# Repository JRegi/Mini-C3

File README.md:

# MiniC3 - PCB

## Description:
MiniC3 is a PCB meant for amateur MiniSumo, featuring:
  -  ESP32-C3 Super Mini 
  -  MP2703 (Mini 360) Step-down module
  -  [Dual TB67H450FNG Driver module](https://github.com/JRegi/Driver-Module-TB67) (or [TA6586 Module](https://github.com/JRegi/Driver-Module-TA6586))

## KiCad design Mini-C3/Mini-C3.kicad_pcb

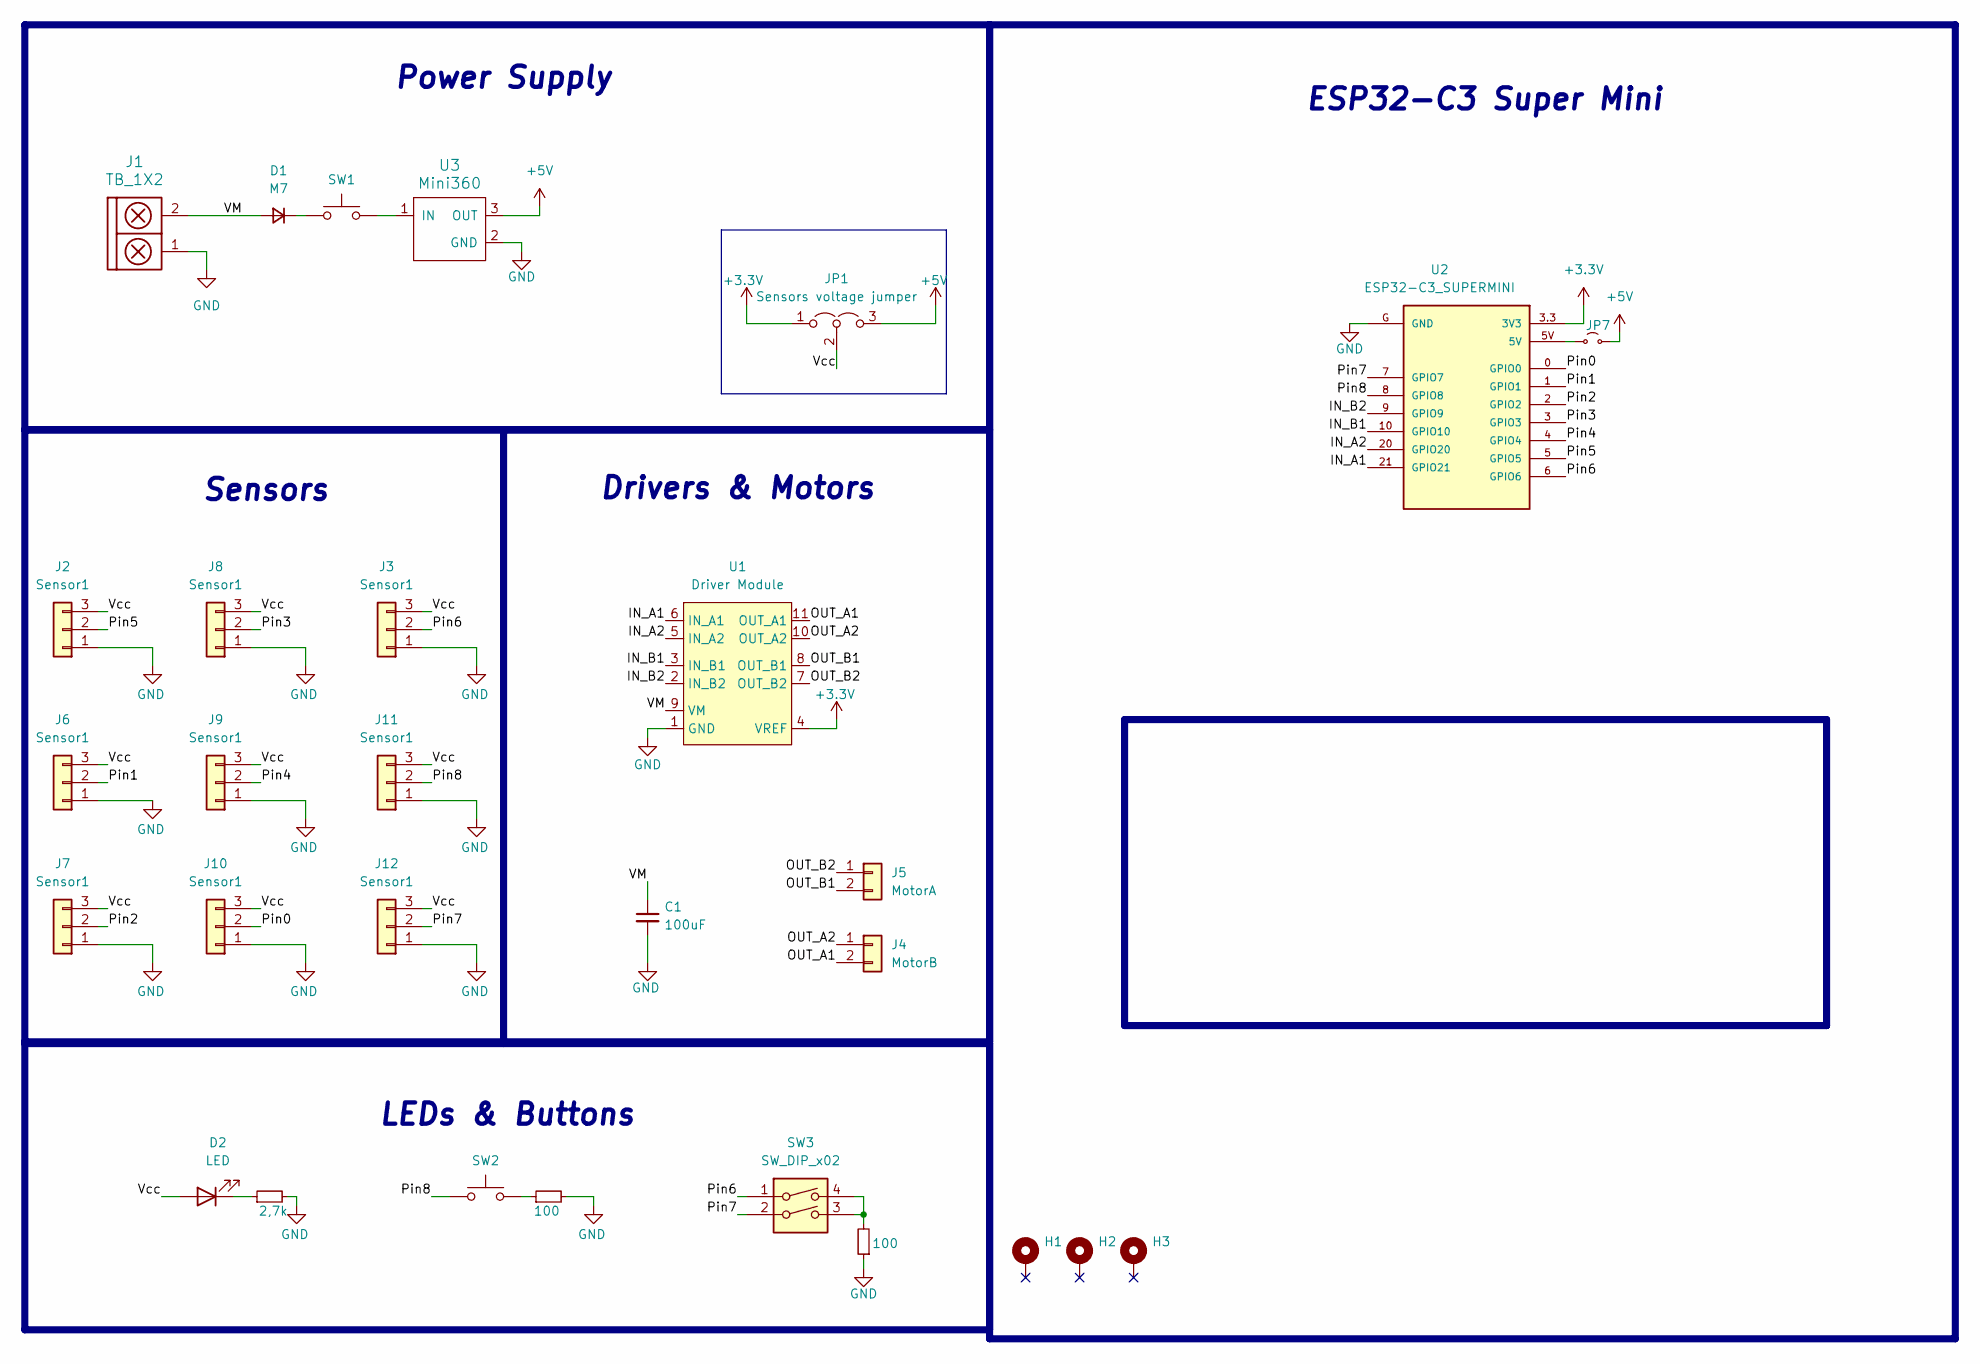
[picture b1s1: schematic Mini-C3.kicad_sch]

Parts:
C1: 100uF; C_Disc_D4.3mm_W1.9mm_P5.00mm
D1: M7; D_SMA
D2: LED; LED_0805_2012Metric
H1, H2, H3: MountingHole_Pad; MountingHole_2.2mm_M2_DIN965_Pad
J1: TB_1X2; MyPinHeader-01x02-vertical
J2, J3, J6, J7, J8, J9, J10, J11, J12: Sensor1; PinHeader_1x03_P2.54-THT
J4: MotorB; MyPinHeader-01x02
J5: MotorA; MyPinHeader-01x02
JP1: Sensors voltage jumper; SolderJumper-3_P2.0mm_Open_TrianglePad1.0x1.5mm
JP7: Jumper_2_Small_Open; SolderJumper-2_P1.3mm_Open_RoundedPad1.0x1.5mm
R1, R2: 100; R_0805_2012Metric
R13: 2,7k; R_0805_2012Metric
SW1: SW_Push; SW_Slide-03_P2.54_L9_W4_H7
SW2: SW_Push; SW_Tactile_SPST_NO_Straight_CK_PTS636Sx25SMTRLFS
SW3: SW_DIP_x02; SW_DIP_SPSTx02_Slide_6.7x6.64mm_W8.61mm_P2.54mm_LowProfile
U1: Driver Module; Dual-Driver-Module
U2: ESP32-C3_SUPERMINI; MODULE_ESP32-C3_SUPERMINI
U3: Mini360; Mini360_step-down

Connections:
+3.3V: JP1.1 (A), U1.4 (VREF), U2.3.3 (3V3)
+5V: JP1.3 (B), JP7.2 (B), U3.3 (OUT)
/IN_A1: U1.6 (IN_A1), U2.21 (GPIO21)
/IN_A2: U1.5 (IN_A2), U2.20 (GPIO20)
/IN_B1: U1.3 (IN_B1), U2.10 (GPIO10)
/IN_B2: U1.2 (IN_B2), U2.9 (GPIO9)
/OUT_A1: J4.2, U1.11 (OUT_A1)
/OUT_A2: J4.1, U1.10 (OUT_A2)
/OUT_B1: J5.2, U1.8 (OUT_B1)
/OUT_B2: J5.1, U1.7 (OUT_B2)
/Pin0: J10.2, U2.0 (GPIO0)
/Pin1: J6.2, U2.1 (GPIO1)
/Pin2: J7.2, U2.2 (GPIO2)
/Pin3: J8.2, U2.3 (GPIO3)
/Pin4: J9.2, U2.4 (GPIO4)
/Pin5: J2.2, U2.5 (GPIO5)
/Pin6: J3.2, SW3.1, U2.6 (GPIO6)
/Pin7: J12.2, SW3.2, U2.7 (GPIO7)
/Pin8: J11.2, SW2.1, U2.8 (GPIO8)
/VM: C1.1, D1.2 (A), J1.2, U1.9 (VM)
/Vcc: D2.2 (A), J2.3, J3.3, J6.3, J7.3, J8.3, J9.3, J10.3, J11.3, J12.3, JP1.2 (C)
GND: C1.2, J1.1, J2.1, J3.1, J6.1, J7.1, J8.1, J9.1, J10.1, J11.1, J12.1, R1.2, R2.1, R13.2, U1.1 (GND), U2.G (GND), U3.2 (GND)
unnamed: D1.1 (K), SW1.2
unnamed: D2.1 (K), R13.1
unnamed: JP7.1 (A), U2.5V
unnamed: R1.1, SW2.2
unnamed: R2.2, SW3.3, SW3.4
unnamed: SW1.1, U3.1 (IN)

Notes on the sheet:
Sensors
Power Supply
LEDs & Buttons
ESP32-C3 Super Mini
Drivers & Motors

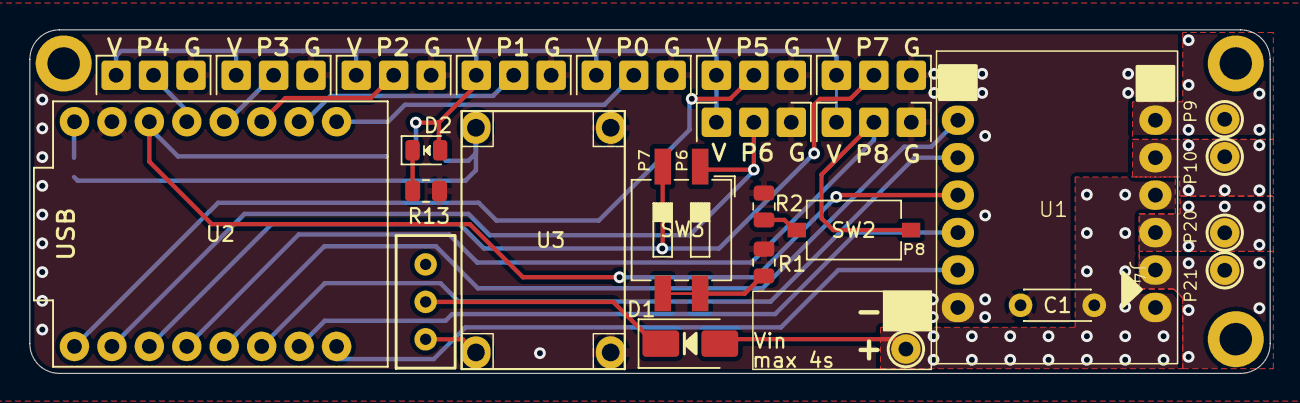
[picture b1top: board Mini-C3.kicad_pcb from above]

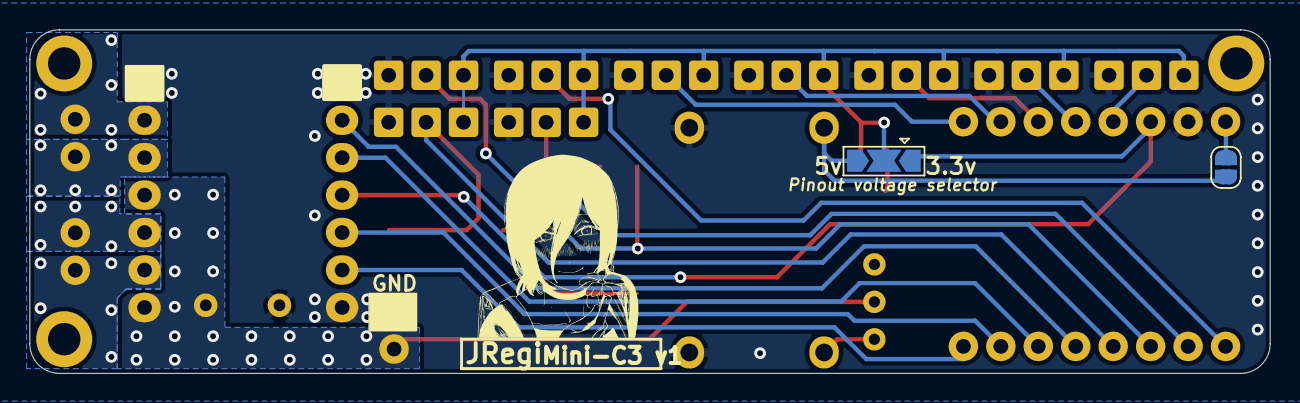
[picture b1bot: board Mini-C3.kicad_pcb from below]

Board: 2 copper layers, 84.1 x 23.3 mm, 29 parts (2 on the bottom side), 28 nets.

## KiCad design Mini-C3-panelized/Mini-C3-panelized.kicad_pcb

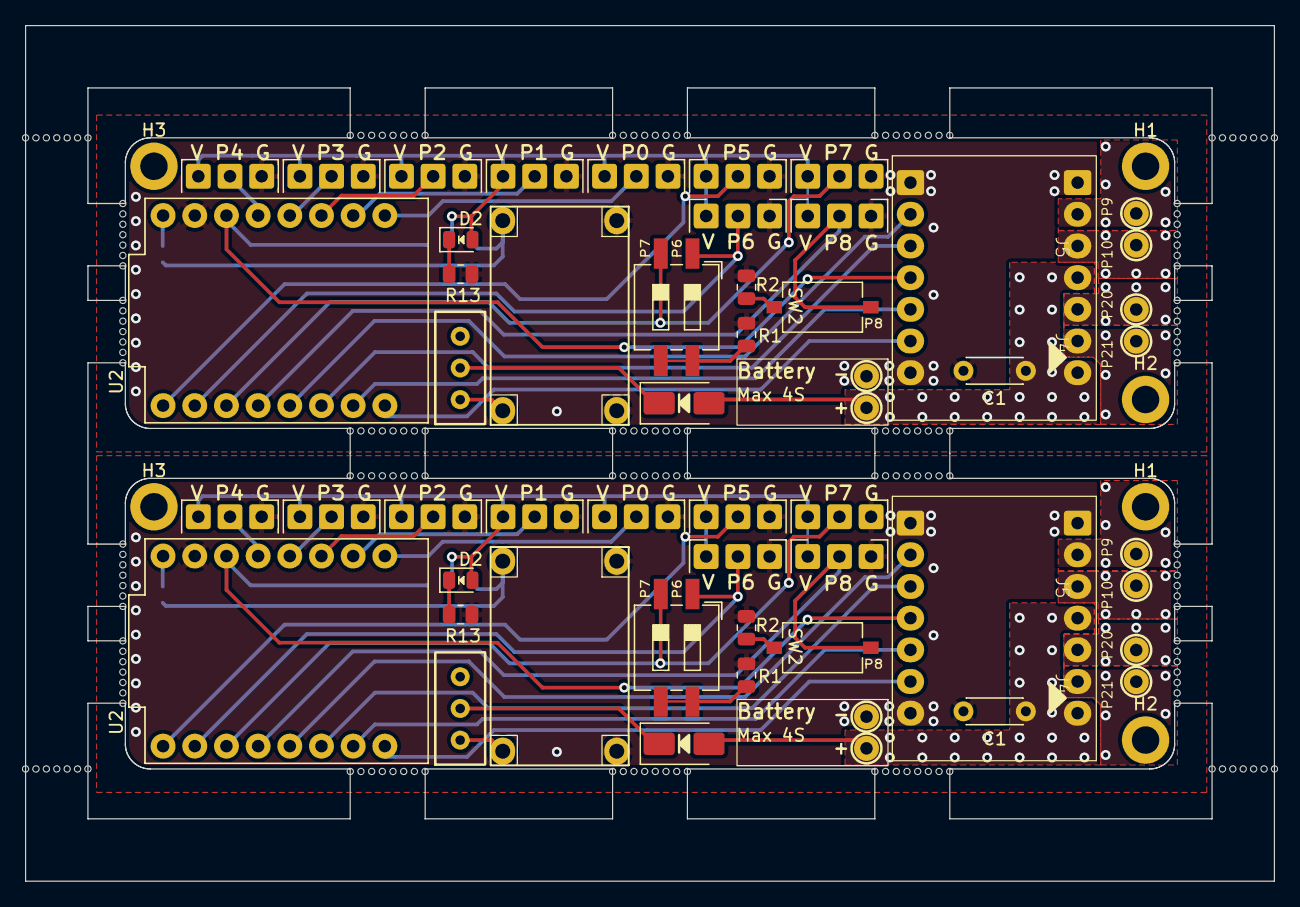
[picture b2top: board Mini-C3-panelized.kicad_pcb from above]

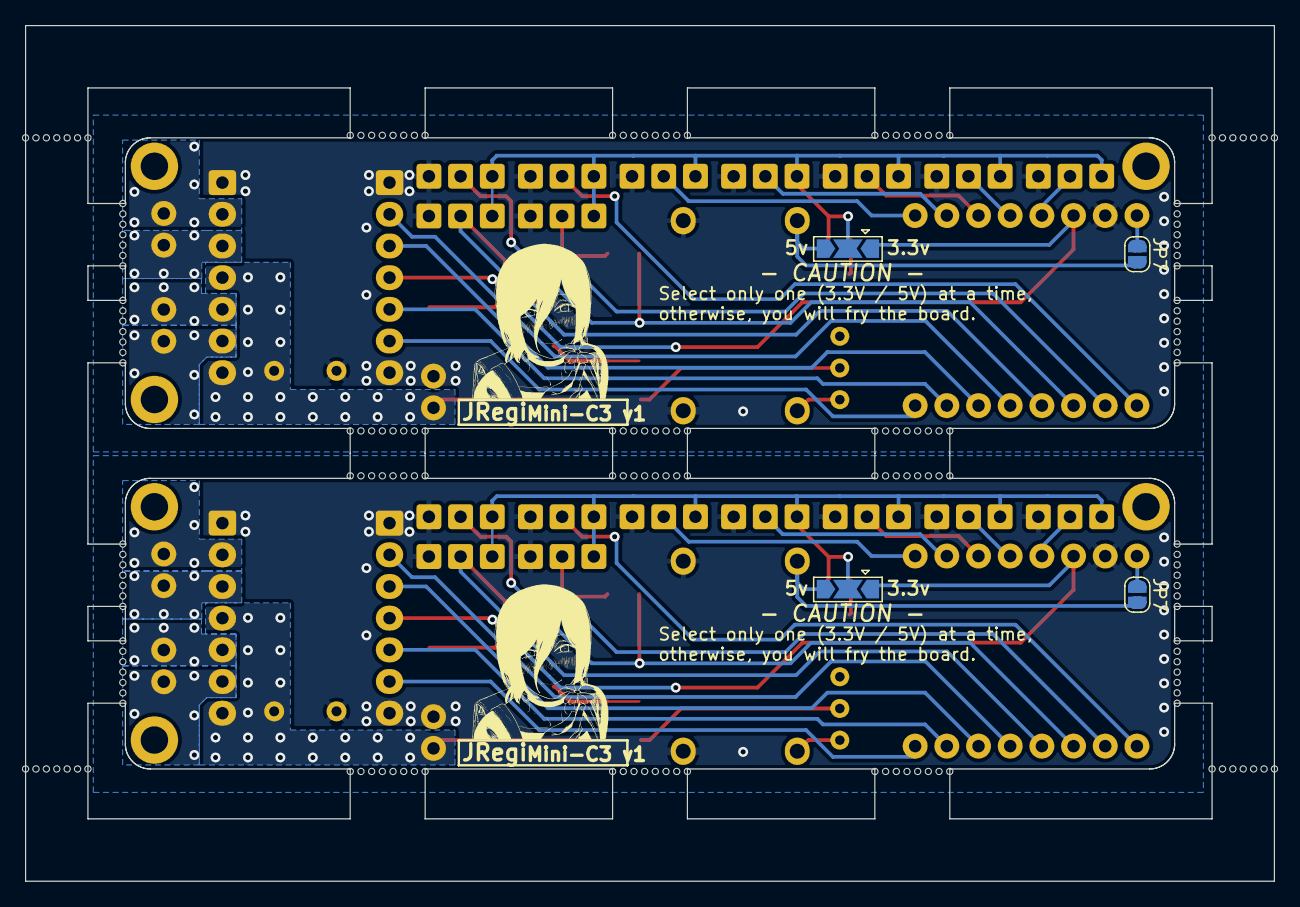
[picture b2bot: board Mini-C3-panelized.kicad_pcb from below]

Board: 2 copper layers, 100.1 x 68.6 mm, 238 parts (4 on the bottom side), 56 nets.

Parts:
C1, C1#2: 100; C_Disc_D4.3mm_W1.9mm_P5.00mm
D1, D1#2: M7; D_SMA
D2, D2#2: LED; LED_0805_2012Metric
H1, H1#2, H2, H2#2, H3, H3#2: MountingHole_Pad; MountingHole_2.2mm_M2_DIN965_Pad
J1, J1#2: TB_1X2; MyPinHeader-01x02-vertical
J2, J2#2, J3, J3#2, J6, J6#2, J7, J7#2, J8, J8#2, J9, J9#2, J10, J10#2, J11, J11#2, J12, J12#2: Sensor1; PinHeader_1x03_P2.54-THT
J4, J4#2: MotorB; MyPinHeader-01x02
J5, J5#2: MotorA; MyPinHeader-01x02
JP1, JP1#2: Sensors voltage jumper; SolderJumper-3_P2.0mm_Open_TrianglePad1.0x1.5mm
JP7, JP7#2: Jumper_2_Small_Open; SolderJumper-2_P1.3mm_Open_RoundedPad1.0x1.5mm
KiKit_MB_1_1, KiKit_MB_1_2, KiKit_MB_1_3, KiKit_MB_1_4, KiKit_MB_1_5, KiKit_MB_1_6, KiKit_MB_1_7, KiKit_MB_2_1, KiKit_MB_2_2, KiKit_MB_2_3, KiKit_MB_2_4, KiKit_MB_2_5, KiKit_MB_2_6, KiKit_MB_2_7, KiKit_MB_3_1, KiKit_MB_3_2, KiKit_MB_3_3, KiKit_MB_3_4, KiKit_MB_3_5, KiKit_MB_3_6, KiKit_MB_3_7, KiKit_MB_4_1, KiKit_MB_4_2, KiKit_MB_4_3, KiKit_MB_4_4, KiKit_MB_4_5, KiKit_MB_4_6, KiKit_MB_4_7, KiKit_MB_5_1, KiKit_MB_5_2, KiKit_MB_5_3, KiKit_MB_5_4, KiKit_MB_5_5, KiKit_MB_5_6, KiKit_MB_5_7, KiKit_MB_5_8, KiKit_MB_6_1, KiKit_MB_6_2, KiKit_MB_6_3, KiKit_MB_6_4, KiKit_MB_6_5, KiKit_MB_6_6, KiKit_MB_6_7, KiKit_MB_6_8, KiKit_MB_7_1, KiKit_MB_7_2, KiKit_MB_7_3, KiKit_MB_7_4, KiKit_MB_7_5, KiKit_MB_7_6, KiKit_MB_7_7, KiKit_MB_7_8, KiKit_MB_8_1, KiKit_MB_8_2, KiKit_MB_8_3, KiKit_MB_8_4, KiKit_MB_8_5, KiKit_MB_8_6, KiKit_MB_8_7, KiKit_MB_8_8, KiKit_MB_9_1, KiKit_MB_9_2, KiKit_MB_9_3, KiKit_MB_9_4, KiKit_MB_9_5, KiKit_MB_9_6, KiKit_MB_9_7, KiKit_MB_9_8, KiKit_MB_10_1, KiKit_MB_10_2, KiKit_MB_10_3, KiKit_MB_10_4, KiKit_MB_10_5, KiKit_MB_10_6, KiKit_MB_10_7, KiKit_MB_10_8, KiKit_MB_11_1, KiKit_MB_11_2, KiKit_MB_11_3, KiKit_MB_11_4, KiKit_MB_11_5, KiKit_MB_11_6, KiKit_MB_11_7, KiKit_MB_12_1, KiKit_MB_12_2, KiKit_MB_12_3, KiKit_MB_12_4, KiKit_MB_12_5, KiKit_MB_12_6, KiKit_MB_12_7, KiKit_MB_13_1, KiKit_MB_13_2, KiKit_MB_13_3, KiKit_MB_13_4, KiKit_MB_13_5, KiKit_MB_13_6, KiKit_MB_13_7, KiKit_MB_14_1, KiKit_MB_14_2, KiKit_MB_14_3, KiKit_MB_14_4, KiKit_MB_14_5, KiKit_MB_14_6, KiKit_MB_14_7, KiKit_MB_15_1, KiKit_MB_15_2, KiKit_MB_15_3, KiKit_MB_15_4, KiKit_MB_15_5, KiKit_MB_15_6, KiKit_MB_15_7, KiKit_MB_15_8, KiKit_MB_16_1, KiKit_MB_16_2, KiKit_MB_16_3, KiKit_MB_16_4, KiKit_MB_16_5, KiKit_MB_16_6, KiKit_MB_16_7, KiKit_MB_16_8, KiKit_MB_17_1, KiKit_MB_17_2, KiKit_MB_17_3, KiKit_MB_17_4, KiKit_MB_17_5, KiKit_MB_17_6, KiKit_MB_17_7, KiKit_MB_17_8, KiKit_MB_18_1, KiKit_MB_18_2, KiKit_MB_18_3, KiKit_MB_18_4, KiKit_MB_18_5, KiKit_MB_18_6, KiKit_MB_18_7, KiKit_MB_18_8, KiKit_MB_19_1, KiKit_MB_19_2, KiKit_MB_19_3, KiKit_MB_19_4, KiKit_MB_19_5, KiKit_MB_19_6, KiKit_MB_19_7, KiKit_MB_19_8, KiKit_MB_20_1, KiKit_MB_20_2, KiKit_MB_20_3, KiKit_MB_20_4, KiKit_MB_20_5, KiKit_MB_20_6, KiKit_MB_20_7, KiKit_MB_20_8, KiKit_MB_21_1, KiKit_MB_21_2, KiKit_MB_21_3, KiKit_MB_21_4, KiKit_MB_21_5, KiKit_MB_21_6, KiKit_MB_21_7, KiKit_MB_22_1, KiKit_MB_22_2, KiKit_MB_22_3, KiKit_MB_22_4, KiKit_MB_22_5, KiKit_MB_22_6, KiKit_MB_22_7, KiKit_MB_23_1, KiKit_MB_23_2, KiKit_MB_23_3, KiKit_MB_23_4, KiKit_MB_23_5, KiKit_MB_23_6, KiKit_MB_23_7, KiKit_MB_24_1, KiKit_MB_24_2, KiKit_MB_24_3, KiKit_MB_24_4, KiKit_MB_24_5, KiKit_MB_24_6, KiKit_MB_24_7: NPTH
R1, R1#2, R2, R2#2: 100; R_0805_2012Metric
R13, R13#2: 2,7k; R_0805_2012Metric
SW1, SW1#2: SW_Push; SW_Slide-03_P2.54_L9_W4_H7
SW2, SW2#2: SW_Push; SW_Tactile_SPST_NO_Straight_CK_PTS636Sx25SMTRLFS
SW3, SW3#2: SW_DIP_x02; SW_DIP_SPSTx02_Slide_6.7x6.64mm_W8.61mm_P2.54mm_LowProfile
U1, U1#2: Driver Module; Dual-Driver-Module
U2, U2#2: ESP32-C3_SUPERMINI; MODULE_ESP32-C3_SUPERMINI
U3, U3#2: Mini360; Mini360_step-down

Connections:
Board_0-+3.3V: JP1.1 (A), U1#2.4 (VREF), U2#2.3.3 (3V3)
Board_0-+5V: JP1.3 (B), JP7.2 (B), U3.3 (OUT)
Board_0-/IN_A1: U1#2.6 (IN_A1), U2#2.21 (GPIO21)
Board_0-/IN_A2: U1#2.5 (IN_A2), U2#2.20 (GPIO20)
Board_0-/IN_B1: U1#2.3 (IN_B1), U2#2.10 (GPIO10)
Board_0-/IN_B2: U1#2.2 (IN_B2), U2#2.9 (GPIO9)
Board_0-/OUT_A1: J4.2, U1#2.11 (OUT_A1)
Board_0-/OUT_A2: J4.1, U1#2.10 (OUT_A2)
Board_0-/OUT_B1: J5.2, U1#2.8 (OUT_B1)
Board_0-/OUT_B2: J5.1, U1#2.7 (OUT_B2)
Board_0-/Pin0: J10#2.2, U2#2.0 (GPIO0)
Board_0-/Pin1: J6#2.2, U2#2.1 (GPIO1)
Board_0-/Pin2: J7#2.2, U2#2.2 (GPIO2)
Board_0-/Pin3: J8#2.2, U2#2.3 (GPIO3)
Board_0-/Pin4: J9.2, U2#2.4 (GPIO4)
Board_0-/Pin5: J2#2.2, U2#2.5 (GPIO5)
Board_0-/Pin6: J3#2.2, SW3#2.1, U2#2.6 (GPIO6)
Board_0-/Pin7: J12.2, SW3#2.2, U2#2.7 (GPIO7)
Board_0-/Pin8: J11#2.2, SW2#2.1, U2#2.8 (GPIO8)
Board_0-/VM: C1#2.1, D1.2 (A), J1#2.2, U1#2.9 (VM)
Board_0-/Vcc: D2.2 (A), J2#2.3, J3#2.3, J6#2.3, J7#2.3, J8#2.3, J9.3, J10#2.3, J11#2.3, J12.3, JP1.2 (C)
Board_0-GND: C1#2.2, J1#2.1, J2#2.1, J3#2.1, J6#2.1, J7#2.1, J8#2.1, J9.1, J10#2.1, J11#2.1, J12.1, R1.2, R2#2.1, R13#2.2, U1#2.1 (GND), U2#2.G (GND), U3.2 (GND)
Board_0-Net-(D1-K): D1.1 (K), SW1#2.2
Board_0-Net-(D2-K): D2.1 (K), R13#2.1
Board_0-Net-(JP7-A): JP7.1 (A), U2#2.5V
Board_0-Net-(R1-Pad1): R1.1, SW2#2.2
Board_0-Net-(R2-Pad2): R2#2.2, SW3#2.3, SW3#2.4
Board_0-Net-(U3-IN): SW1#2.1, U3.1 (IN)
Board_1-+3.3V: JP1#2.1 (A), U1.4 (VREF), U2.3.3 (3V3)
Board_1-+5V: JP1#2.3 (B), JP7#2.2 (B), U3#2.3 (OUT)
Board_1-/IN_A1: U1.6 (IN_A1), U2.21 (GPIO21)
Board_1-/IN_A2: U1.5 (IN_A2), U2.20 (GPIO20)
Board_1-/IN_B1: U1.3 (IN_B1), U2.10 (GPIO10)
Board_1-/IN_B2: U1.2 (IN_B2), U2.9 (GPIO9)
Board_1-/OUT_A1: J4#2.2, U1.11 (OUT_A1)
Board_1-/OUT_A2: J4#2.1, U1.10 (OUT_A2)
Board_1-/OUT_B1: J5#2.2, U1.8 (OUT_B1)
Board_1-/OUT_B2: J5#2.1, U1.7 (OUT_B2)
Board_1-/Pin0: J10.2, U2.0 (GPIO0)
Board_1-/Pin1: J6.2, U2.1 (GPIO1)
Board_1-/Pin2: J7.2, U2.2 (GPIO2)
Board_1-/Pin3: J8.2, U2.3 (GPIO3)
Board_1-/Pin4: J9#2.2, U2.4 (GPIO4)
Board_1-/Pin5: J2.2, U2.5 (GPIO5)
Board_1-/Pin6: J3.2, SW3.1, U2.6 (GPIO6)
Board_1-/Pin7: J12#2.2, SW3.2, U2.7 (GPIO7)
Board_1-/Pin8: J11.2, SW2.1, U2.8 (GPIO8)
Board_1-/VM: C1.1, D1#2.2 (A), J1.2, U1.9 (VM)
Board_1-/Vcc: D2#2.2 (A), J2.3, J3.3, J6.3, J7.3, J8.3, J9#2.3, J10.3, J11.3, J12#2.3, JP1#2.2 (C)
Board_1-GND: C1.2, J1.1, J2.1, J3.1, J6.1, J7.1, J8.1, J9#2.1, J10.1, J11.1, J12#2.1, R1#2.2, R2.1, R13.2, U1.1 (GND), U2.G (GND), U3#2.2 (GND)
Board_1-Net-(D1-K): D1#2.1 (K), SW1.2
Board_1-Net-(D2-K): D2#2.1 (K), R13.1
Board_1-Net-(JP7-A): JP7#2.1 (A), U2.5V
Board_1-Net-(R1-Pad1): R1#2.1, SW2.2
Board_1-Net-(R2-Pad2): R2.2, SW3.3, SW3.4
Board_1-Net-(U3-IN): SW1.1, U3#2.1 (IN)

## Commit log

2024-09-09 KiCad project
    Added the KiCad project and updated the schematic.
2024-09-09 schematic & pcb
    ESP32-C3 pinout img added. The schematic is almost done.
2024-09-12 PCB components placement
    Improved the placement of the components.
2024-09-12 pecebé
2024-09-12 la pecebé
2024-09-13 PCB almost there
2024-09-15 Repositioned & added footprints
    Honestly there's so much that was done that I just can't put it all here, also maybe because I don't remember. You should see the changes for yourself. Who reads these anyway?
2024-09-15 Pin names
2024-09-15 testCommit
2024-09-16 gerbers
2024-09-16 fixme
2024-09-16 Update README & deleted useless files
2024-09-16 panels
2024-09-16 panels again
2024-09-17 silkscreen and gerber files again
2024-09-19 yet another gerber files update
2024-09-19 regenerated gerber files
2024-10-11 Schematic change
2024-11-04 3D Files
